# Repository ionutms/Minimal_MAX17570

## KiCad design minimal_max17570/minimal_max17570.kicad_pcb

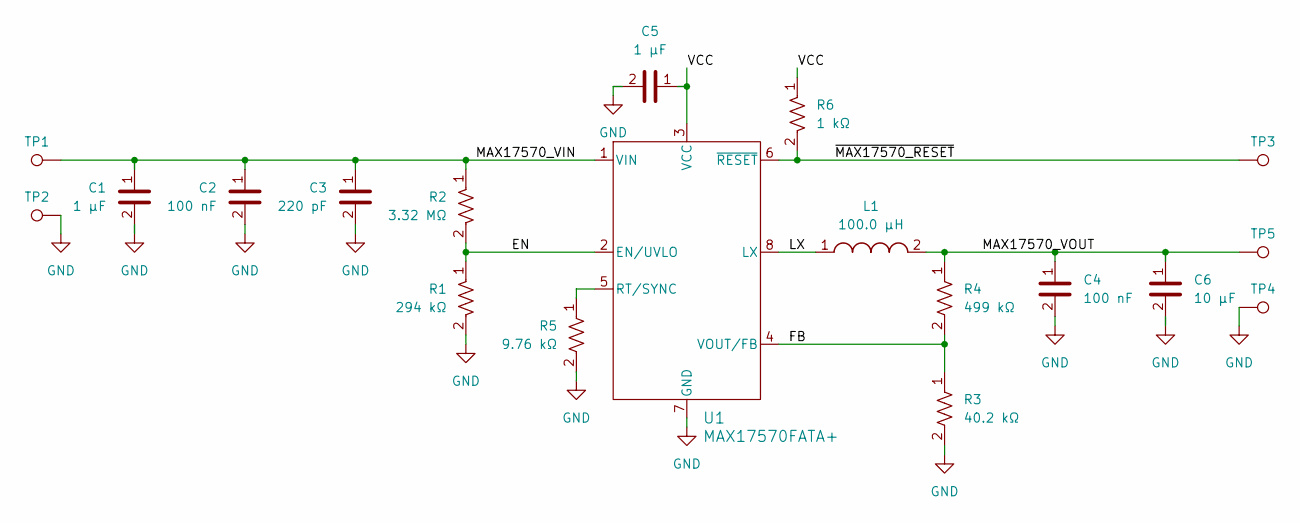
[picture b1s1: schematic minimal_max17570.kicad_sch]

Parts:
C1: 1 µF; C_0805_2012Metric; Tolerance 10%; Voltage Rating 100V; MPN GRJ21BC72A105KE11L
C2, C4: 100 nF; C_0603_1608Metric; Tolerance 10%; Voltage Rating 100V; MPN C1608X7S2A104K080AB
C3: 220 pF; C_0402_1005Metric; Tolerance 5%; Voltage Rating 100V; MPN CGA2B2NP02A221J050BA
C5: 1 µF; C_0402_1005Metric; Tolerance 10%; Voltage Rating 16V; MPN C1005X6S1C105K050BC
C6: 10 µF; C_1206_3216Metric; Tolerance 10%; Voltage Rating 50V; MPN CL31B106KBHNNN#
L1: 100.0 µH; 74404054; Tolerance ±20%; MPN 74404054101
R1: 294 kΩ; R_0402_1005Metric; Tolerance 1%; Voltage Rating 50V; MPN ERJ-2RKF2943X
R2: 3.32 MΩ; R_0402_1005Metric; Tolerance 1%; Voltage Rating 50V; MPN RC0402FR-073M32L
R3: 40.2 kΩ; R_0402_1005Metric; Tolerance 1%; Voltage Rating 50V; MPN ERJ-2RKF4022X
R4: 499 kΩ; R_0402_1005Metric; Tolerance 1%; Voltage Rating 50V; MPN ERJ-2RKF4993X
R5: 9.76 kΩ; R_0402_1005Metric; Tolerance 1%; Voltage Rating 50V; MPN ERJ-2RKF9761X
R6: 1 kΩ; R_0402_1005Metric; Tolerance 1%; Voltage Rating 50V; MPN ERJ-2RKF1001X
TP1, TP2, TP3, TP4, TP5: TestPoint; TestPoint_THTPad_Castelated
U1: MAX17570FATA+; 21-100514_T822C&plus_6C_ADI; MPN MAX17570FATA+

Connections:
/EN: R1.1, R2.2, U1.2 (EN/UVLO)
/FB: R3.1, R4.2, U1.4 (VOUT/FB)
/LX: L1.1, U1.8 (LX)
/MAX17570_VIN: C1.1, C2.1, C3.1, R2.1, TP1.1, U1.1 (VIN)
/MAX17570_VOUT: C4.1, C6.1, L1.2, R4.1, TP5.1
/VCC: C5.1, R6.1, U1.3 (VCC)
/~MAX17570_RESET: R6.2, TP3.1, U1.6 (~RESET)
GND: C1.2, C2.2, C3.2, C4.2, C5.2, C6.2, R1.2, R3.2, R5.2, TP2.1, TP4.1, U1.7 (GND)
unnamed: R5.1, U1.5 (RT/SYNC)

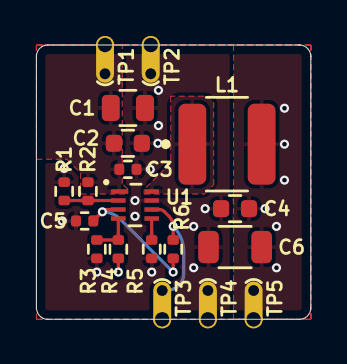
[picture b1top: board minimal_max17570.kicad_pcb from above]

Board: 4 copper layers, 15.2 x 15.2 mm, 19 parts (0 on the bottom side), 9 nets.

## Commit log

2025-08-25 Add KiCad project files and GitHub workflows for documentation and 3D model generation
2025-08-25 Update KiCad documentation for minimal_max17570 (schematics and PCB renders)
2025-08-25 backup
2025-08-28 Update KiCad Docker image version and add Interactive HTML BOM generation
2025-10-05 chore: update workflows from central repository
2025-10-05 chore: update workflows and kicad config from central repository
2025-10-26 Update kicad-config workflow settings
